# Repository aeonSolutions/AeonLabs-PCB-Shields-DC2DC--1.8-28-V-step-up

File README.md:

# AeonLabs PCB Shields DC DC 1.8-28V Step up
This is a pcb design for a DC DC [1.8;28]V step-up converter intended for small, low power, applications/ devices.. Suitable as a add-on design for any other KiCad project. The MT3608 is a constant frequency, 6-pin SOT23 with hight efficiency up to 97%. To change the output voltage one needs to change the resistance in the voltage divider connected to pin 3 of the MT3608 IC.

*Don't forget to LIKE , SHARE and subscribe the free whatsApp group* and if you liked this PCB consider buying me a cup of coffee. Links below.

### Status
  fully tested & working.

If you already tested this PCB send me a message. Thank you

## Revisions
- revision 1.0
 
## Download options
Download this repository if you need the KiCad Files or, download the Gerber files in the release section of this repository

## Liked it ? Get a Free PCB for yourself
Send me your Device or hardware and i will design a custom PCB for it. Free of charge. Contact-me on WhatsApp or email for more info. 

## Q&A WhatsApp Group
If you have any Questions or simply  like this kind of projects and want to stay updated with the latest research ideas and prototypes during the day and week, join the WhatsApp Group
[A.I. Things](https://chat.whatsapp.com/FkNC7u83kuy2QRA5sqjBVg)

## Fully assembled PCB
Alternatively, and if you do not want to build a PCB by yourself and like to buy one, you can do it here:

The price will be around 30eur plus postage fees.
(I will also deliver the assembled PCB with all the components in place at a fair aditonal cost).

#### Be supportive of my dedication and work towards technology education and buy me a coffee. Link below.

________________________________________________________________________________________________________________

## PCB Parts list
- [Capacitor 2.2uF SMD](https://s.click.aliexpress.com/e/_AVdmzr)
- [Resistor SMD 1206 ](https://s.click.aliexpress.com/e/_A7OXrR)
- [SS34 rectifier Diode](https://s.click.aliexpress.com/e/_DkhOib9)
- [MT3608 DC DC 5W 2A](https://s.click.aliexpress.com/e/_Dmd5xxh)
- [SMD inductor]( https://s.click.aliexpress.com/e/_Dlx2YWx)

## Firmware Download 
one can use the PCB in the repository [AeonLabs-MCU-Burner-USB-to-UART-TTL](https://github.com/aeonSolutions/AeonLabs-MCU-Burner-USB-to-UART-TTL) to program the ESP32 WROOM32 MCU on this PCB.

## REWORKING MT3608 BOOST CONVERTERS FOR LOWER IDLE CURRENT DRAW
by [Lewin Day](https://hackaday.com/author/lewinday/) and by [Aka Kasyan](https://www.youtube.com/c/KasyanTV)

One drawback of the MT3608 IC, particularly when working with batteries, is the idle current draw, on the order of 1 to 1.5mA. Fear not, however — there is a workaround, courtesy of [Aka Kasyan]. (Video, embedded below.)

The trick is to modify the behavior of the converter when no load is connected. The enable pin of the boost converter is held low through a pull-down resistor, keeping the boost converter switched off. In this state, the output voltage is equal to the input voltage. A current sense resistor is then installed in the output path. When a load is connected, this causes a voltage drop across the current sense resistor. This is then used to switch a transistor, which then connects the enable pin to the positive rail, switching the converter on, leading to the full boosted output voltage being reached.

Aka Kasyan reports that this drastically cuts the idle current draw, which is particularly useful for battery powered projects. It’s important to note that the current sense resistor must be appropriately sized for the given load, however. 

______________________________________________________________________________________________________________________________

### License
2022 Creative Commons Attribution-NonCommercial-ShareAlike 4.0 International

https://creativecommons.org/licenses/by-nc-sa/4.0/

### Own a copy of this work
if you like to own a copy of this work, you can buy it as a NFT or Ethereum. contact me for more details at mtpsilva@gmail.com
________________________________________________________________________________________________________________
## [Go back to main catalogue page](https://github.com/aeonSolutions/PCB-Prototyping-Catalogue)
________________________________________________________________________________________________________________

### Share this PCB board files

### Be supportive of my dedication and work towards technology education and buy me a coffee

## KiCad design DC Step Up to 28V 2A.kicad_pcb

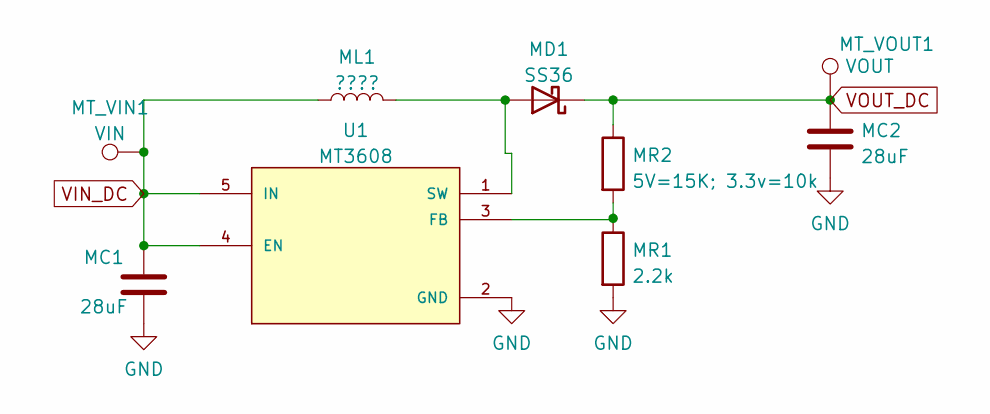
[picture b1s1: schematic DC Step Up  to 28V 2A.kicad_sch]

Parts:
MC1, MC2: 28uF; C_0805_2012Metric_Pad1.18x1.45mm_HandSolder
MD1: SS36; D_2010_5025Metric_Pad1.52x2.65mm_HandSolder
ML1: ????; L_0805_2012Metric_Pad1.15x1.40mm_HandSolder
MR1: 2.2k; R_0805_2012Metric_Pad1.20x1.40mm_HandSolder
MR2: 5V=15K; 3.3v=10k; R_0805_2012Metric_Pad1.20x1.40mm_HandSolder
MT_VIN1: VIN; TestPoint_Pad_D1.5mm
MT_VOUT1: VOUT; TestPoint_Pad_D1.5mm
U1: MT3608; MT3608 SOT95P280X145-6N; PARTREV 1.0

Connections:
GND: MC1.2, MC2.2, MR1.2, U1.2 (GND)
unnamed: MR1.1, MR2.2, U1.3 (FB)
unnamed: MD1.2 (A), ML1.2, U1.1 (SW)
VIN_DC: MC1.1, ML1.1, MT_VIN1.1, U1.4 (EN), U1.5 (IN)
VOUT_DC: MC2.1, MD1.1 (K), MR2.1, MT_VOUT1.1

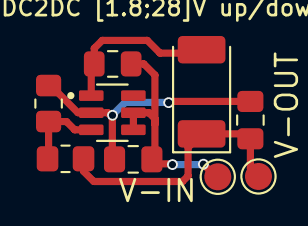
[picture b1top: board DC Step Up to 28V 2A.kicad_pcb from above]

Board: 2 copper layers, 9 parts (0 on the bottom side), 5 nets.

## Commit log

2022-06-26 rev 1.0
